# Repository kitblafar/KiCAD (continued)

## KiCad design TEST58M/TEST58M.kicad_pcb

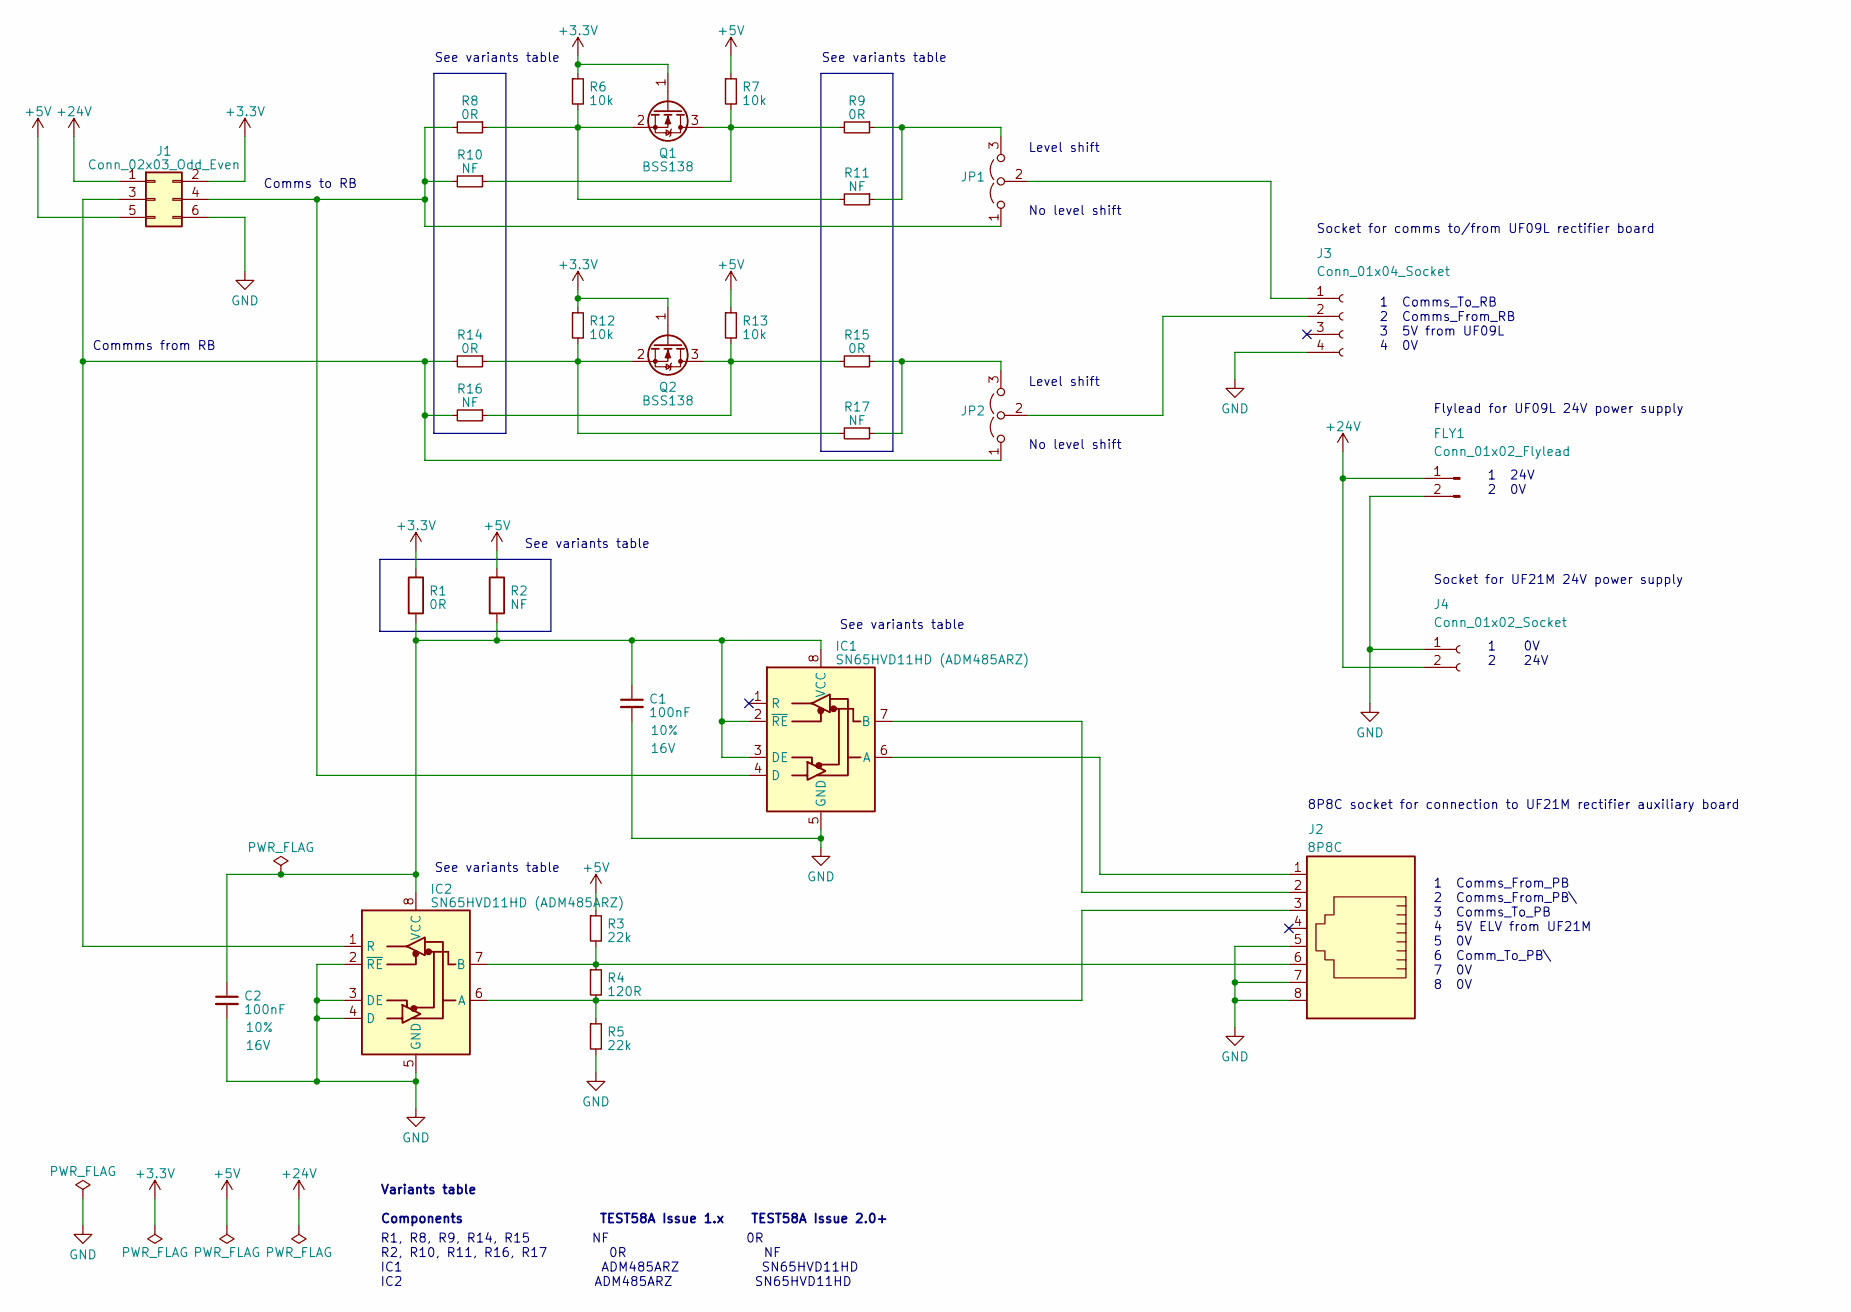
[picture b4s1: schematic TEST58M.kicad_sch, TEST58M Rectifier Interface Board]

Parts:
C1, C2: 100nF; C_0805_2012Metric_Pad1.18x1.45mm_HandSolder; Tolerance 10%; Voltage 16V
FLY1: Conn_01x02_Flylead; A2051-2P
IC1, IC2: SN65HVD11HD (ADM485ARZ); SOIC-8_3.9x4.9mm_P1.27mm
J1: Conn_02x03_Odd_Even; CSB0201
J2: 8P8C; RJ45Conn
J3: Conn_01x04_Socket; A2051-4P
J4: Conn_01x02_Socket; ECH381V
JP1, JP2: PinHeader_1x03_P2.54mm_Vertical
Q1, Q2: BSS138; SOT-23
R1, R8, R9, R14, R15: 0R; R_0805_2012Metric_Pad1.20x1.40mm_HandSolder; Tolerance 0%
R2, R10, R11, R16, R17: NF; R_0805_2012Metric_Pad1.20x1.40mm_HandSolder
R3, R5: 22k; R_1206_3216Metric_Pad1.30x1.75mm_HandSolder
R4: 120R; R_1206_3216Metric_Pad1.30x1.75mm_HandSolder
R6, R7, R12, R13: 10k; R_0805_2012Metric_Pad1.20x1.40mm_HandSolder

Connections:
+3.3V: J1.2, Q1.1 (G), Q2.1 (G), R1.1, R6.1, R12.1
+5V: J1.5, R2.1, R3.1, R7.1, R13.1
+24V: FLY1.1, J1.1, J4.2
GND: C1.2, C2.2, FLY1.2, IC1.5 (GND), IC2.2 (~RE), IC2.3 (DE), IC2.4 (D), IC2.5 (GND), J1.6, J2.5, J2.7, J2.8, J3.4, J4.1, R5.2
unnamed: IC1.6 (A), J2.1
unnamed: IC1.7 (B), J2.2
unnamed: IC1.4 (D), J1.4, JP1.1 (A), R8.2, R10.2
unnamed: C1.1, C2.1, IC1.2 (~RE), IC1.3 (DE), IC1.8 (VCC), IC2.8 (VCC), R1.2, R2.2
unnamed: IC2.6 (A), J2.3, R4.2, R5.1
unnamed: IC2.7 (B), J2.6, R3.2, R4.1
unnamed: IC2.1 (R), J1.3, JP2.1 (A), R14.2, R16.2
unnamed: J3.1, JP1.2 (C)
unnamed: J3.2, JP2.2 (C)
unnamed: JP1.3 (B), R9.1, R11.1
unnamed: JP2.3 (B), R15.1, R17.1
unnamed: Q1.3 (D), R7.2, R9.2, R10.1
unnamed: Q1.2 (S), R6.2, R8.1, R11.2
unnamed: Q2.3 (D), R13.2, R15.2, R16.1
unnamed: Q2.2 (S), R12.2, R14.1, R17.2

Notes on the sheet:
Variants table Components TEST58A Issue 1.x TEST58A Issue 2.0+
1 0V 2 24V
Commms from RB
See variants table
Level shift
Socket for comms to/from UF09L rectifier board
No level shift
Comms to RB
8P8C socket for connection to UF21M rectifier auxiliary board
Flylead for UF09L 24V power supply
Socket for UF21M 24V power supply
1 24V 2 0V
R1, R8, R9, R14, R15 NF 0R R2, R10, R11, R16, R17 0R NF IC1 ADM485ARZ SN65HVD11HD IC2 ADM485ARZ SN65HVD11HD
1 Comms_To_RB 2 Comms_From_RB 3 5V from UF09L 4 0V
1 Comms_From_PB 2 Comms_From_PB\ 3 Comms_To_PB 4 5V ELV from UF21M 5 0V 6 Comm_To_PB\ 7 0V 8 0V

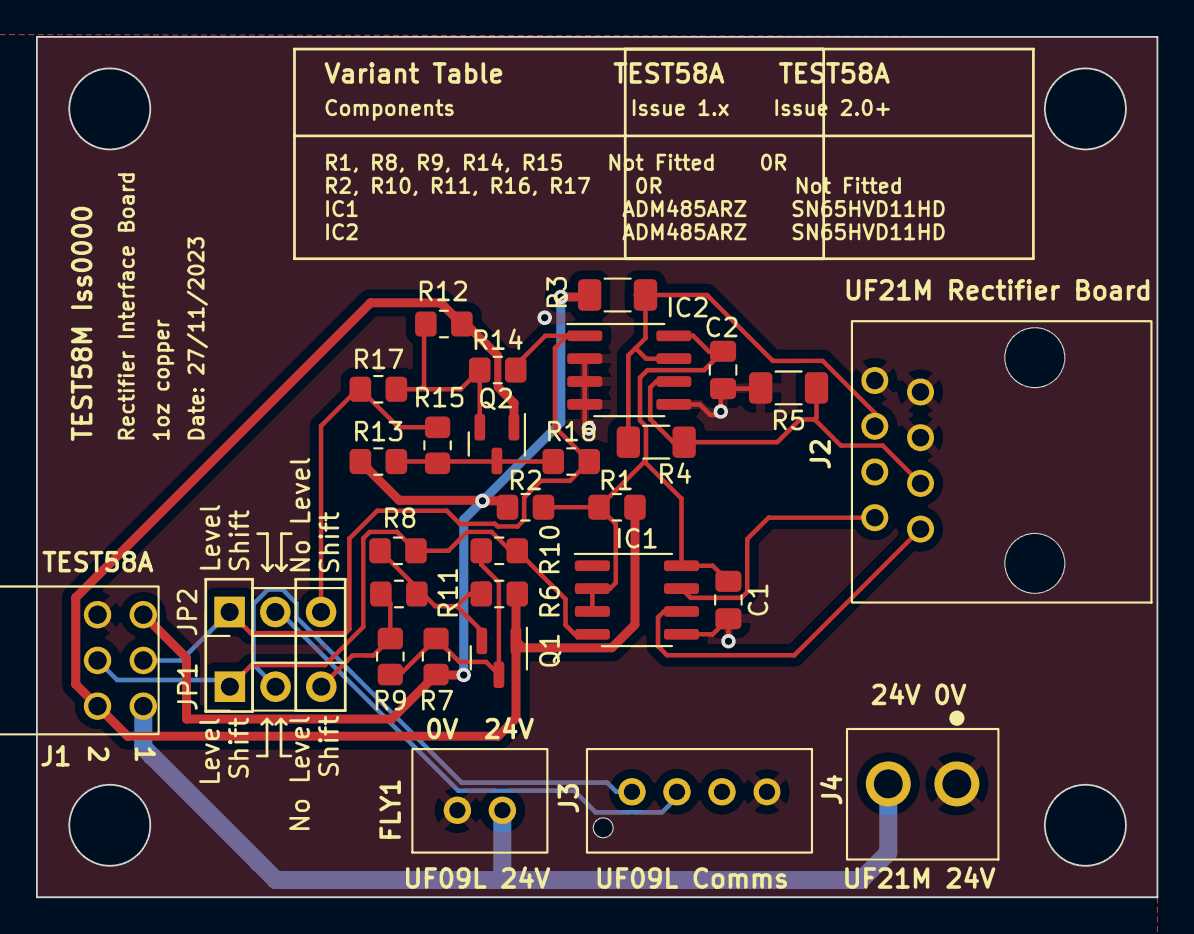
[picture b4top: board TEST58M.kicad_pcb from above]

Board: 2 copper layers, 62.2 x 47.8 mm, 30 parts (0 on the bottom side), 19 nets.

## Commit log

2023-08-16 TEST141- Manufacturing Test Board
    Includes:
    - Gerbers: manufacturing Gerbers for each copper weight and finish
    - PANELTEST141: the complete and populated panel
    - TEST141: complete single circuit
    - TEST141_GeneratePanel: bare single circuit with KiKit markers for panel generation with KiKit
    - TEST141_Iss0000_ManPack: First KiCAD CT standard Manpack
2023-09-14 Run 2_Update 1
    TEST141 updated to include and EMC bracket
    Update to come: new USB-C part
2023-09-18 KiCADGuide_Is0000
    KiCAD workflow guide complete with associated KiCAD fixer program
2023-10-17 Run 2 Ordered
    The second run of the test order:
    - changed position of components to fit the EMC disconnect bracket on
    - EMC disconnect added
    - USB-C cell updated
2023-12-06 TEST58M Created
    Board for Rob, 1Oz copper, 2 layer (basic)
2024-01-17 GAVIM moved to KiCAD
    - A beautiful GAVIM re-lay out (truly blessed)
    - Not yet reviewed by Ed
2024-11-12 Updates to TEST137
